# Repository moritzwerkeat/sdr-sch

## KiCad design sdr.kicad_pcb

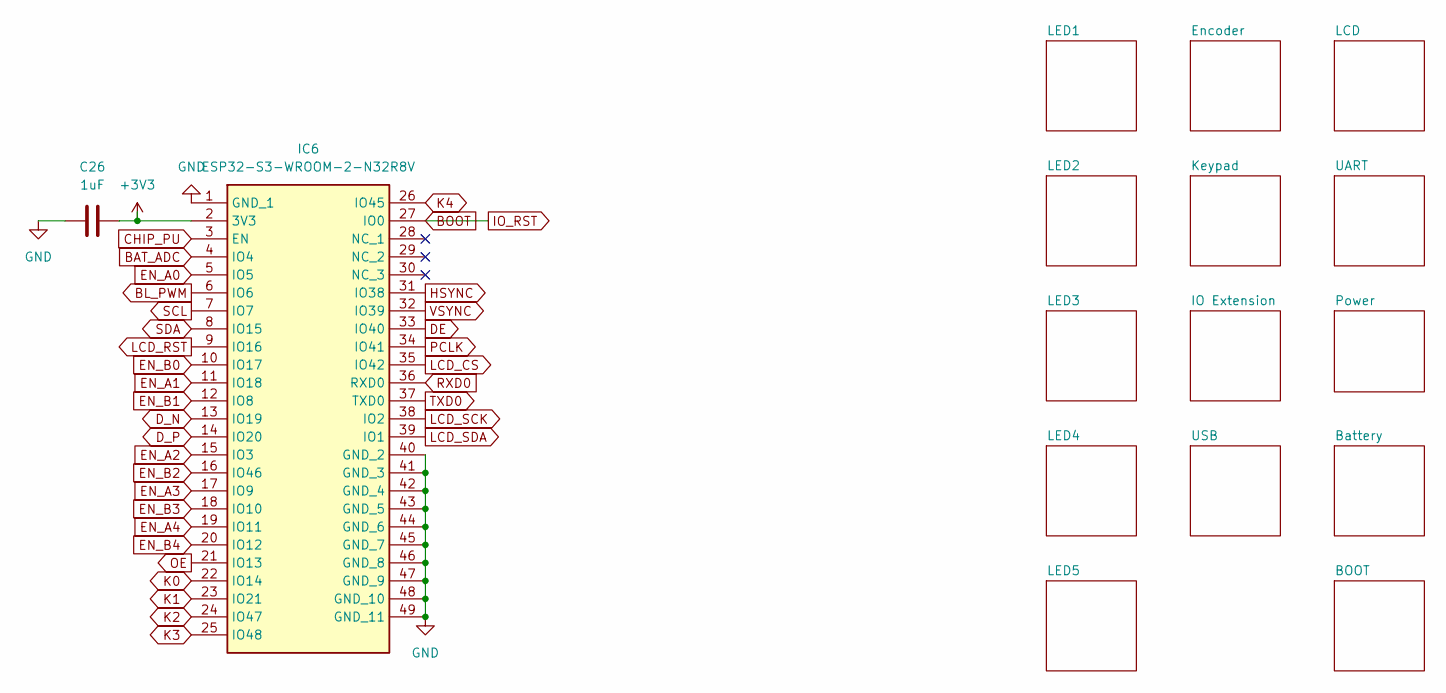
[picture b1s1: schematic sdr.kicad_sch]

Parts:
C26: 1uF; C_0603_1608Metric
IC6: ESP32-S3-WROOM-2-N32R8V; ESP32S3WROOM2N32R8V; Manufacturer_Part_Number ESP32-S3-WROOM-2-N32R8V; Mouser Part Number 356-ESP3S3WRM2N32R8V

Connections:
+3V3: C26.1, IC6.2 (3V3); also elsewhere on the board
BAT_ADC: IC6.4 (IO4); also elsewhere on the board
BL_PWM: IC6.6 (IO6); also elsewhere on the board
BOOT: IC6.27 (IO0); also elsewhere on the board
CHIP_PU: IC6.3 (EN); also elsewhere on the board
DE: IC6.33 (IO40); also elsewhere on the board
D_N: IC6.13 (IO19); also elsewhere on the board
D_P: IC6.14 (IO20); also elsewhere on the board
EN_A0: IC6.5 (IO5); also elsewhere on the board
EN_A1: IC6.11 (IO18); also elsewhere on the board
EN_A2: IC6.15 (IO3); also elsewhere on the board
EN_A3: IC6.17 (IO9); also elsewhere on the board
EN_A4: IC6.19 (IO11); also elsewhere on the board
EN_B0: IC6.10 (IO17); also elsewhere on the board
EN_B1: IC6.12 (IO8); also elsewhere on the board
EN_B2: IC6.16 (IO46); also elsewhere on the board
EN_B3: IC6.18 (IO10); also elsewhere on the board
EN_B4: IC6.20 (IO12); also elsewhere on the board
GND: C26.2, IC6.1 (GND_1), IC6.40 (GND_2), IC6.41 (GND_3), IC6.42 (GND_4), IC6.43 (GND_5), IC6.44 (GND_6), IC6.45 (GND_7), IC6.46 (GND_8), IC6.47 (GND_9), IC6.48 (GND_10), IC6.49 (GND_11); also elsewhere on the board
HSYNC: IC6.31 (IO38); also elsewhere on the board
K0: IC6.22 (IO14); also elsewhere on the board
K1: IC6.23 (IO21); also elsewhere on the board
K2: IC6.24 (IO47); also elsewhere on the board
K3: IC6.25 (IO48); also elsewhere on the board
K4: IC6.26 (IO45); also elsewhere on the board
LCD_CS: IC6.35 (IO42); also elsewhere on the board
LCD_RST: IC6.9 (IO16); also elsewhere on the board
LCD_SCK: IC6.38 (IO2); also elsewhere on the board
LCD_SDA: IC6.39 (IO1); also elsewhere on the board
OE: IC6.21 (IO13); also elsewhere on the board
PCLK: IC6.34 (IO41); also elsewhere on the board
RXD0: IC6.36 (RXD0); also elsewhere on the board
SCL: IC6.7 (IO7); also elsewhere on the board
SDA: IC6.8 (IO15); also elsewhere on the board
TXD0: IC6.37 (TXD0); also elsewhere on the board
VSYNC: IC6.32 (IO39); also elsewhere on the board

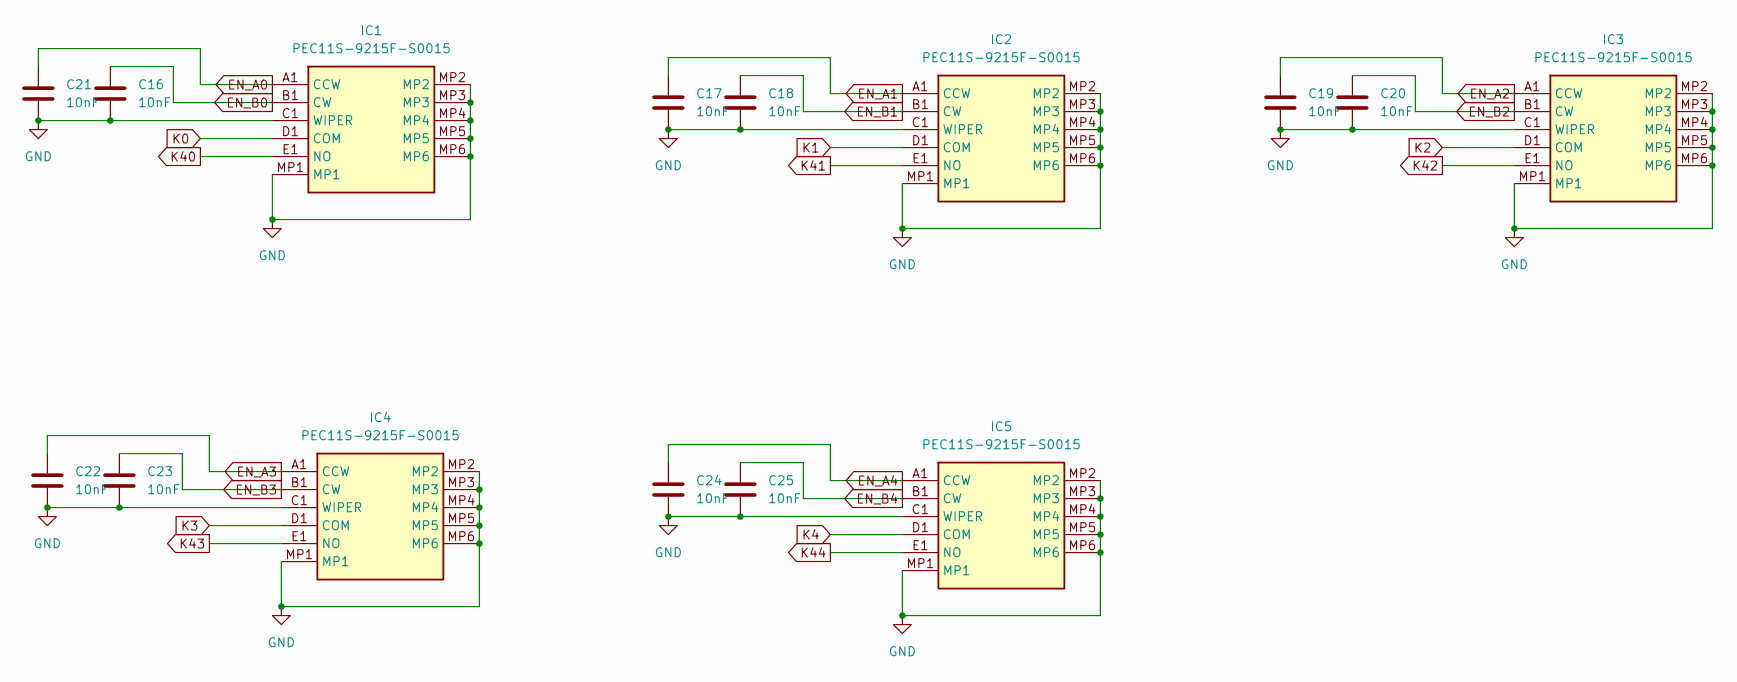
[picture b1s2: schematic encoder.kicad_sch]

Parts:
C16, C17, C18, C19, C20, C21, C22, C23, C24, C25: 10nF; C_0603_1608Metric
IC1, IC2, IC3, IC4, IC5: PEC11S-9215F-S0015; PEC11S9215FS0015; Manufacturer_Part_Number PEC11S-9215F-S0015; Mouser Part Number 652-PEC11S9215FS0015

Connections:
EN_A0: C21.1, IC1.A1 (CCW); also elsewhere on the board
EN_A1: C17.1, IC2.A1 (CCW); also elsewhere on the board
EN_A2: C19.1, IC3.A1 (CCW); also elsewhere on the board
EN_A3: C22.1, IC4.A1 (CCW); also elsewhere on the board
EN_A4: C24.1, IC5.A1 (CCW); also elsewhere on the board
EN_B0: C16.1, IC1.B1 (CW); also elsewhere on the board
EN_B1: C18.1, IC2.B1 (CW); also elsewhere on the board
EN_B2: C20.1, IC3.B1 (CW); also elsewhere on the board
EN_B3: C23.1, IC4.B1 (CW); also elsewhere on the board
EN_B4: C25.1, IC5.B1 (CW); also elsewhere on the board
GND: C16.2, C17.2, C18.2, C19.2, C20.2, C21.2, C22.2, C23.2, C24.2, C25.2, IC1.C1 (WIPER), IC1.MP1, IC1.MP2, IC1.MP3, IC1.MP4, IC1.MP5, IC1.MP6, IC2.C1 (WIPER), IC2.MP1, IC2.MP2, IC2.MP3, IC2.MP4, IC2.MP5, IC2.MP6, IC3.C1 (WIPER), IC3.MP1, IC3.MP2, IC3.MP3, IC3.MP4, IC3.MP5, IC3.MP6, IC4.C1 (WIPER), IC4.MP1, IC4.MP2, IC4.MP3, IC4.MP4, IC4.MP5, IC4.MP6, IC5.C1 (WIPER), IC5.MP1, IC5.MP2, IC5.MP3, IC5.MP4, IC5.MP5, IC5.MP6; also elsewhere on the board
K0: IC1.D1 (COM); also elsewhere on the board
K1: IC2.D1 (COM); also elsewhere on the board
K2: IC3.D1 (COM); also elsewhere on the board
K3: IC4.D1 (COM); also elsewhere on the board
K4: IC5.D1 (COM); also elsewhere on the board
K40: IC1.E1 (NO); also elsewhere on the board
K41: IC2.E1 (NO); also elsewhere on the board
K42: IC3.E1 (NO); also elsewhere on the board
K43: IC4.E1 (NO); also elsewhere on the board
K44: IC5.E1 (NO); also elsewhere on the board

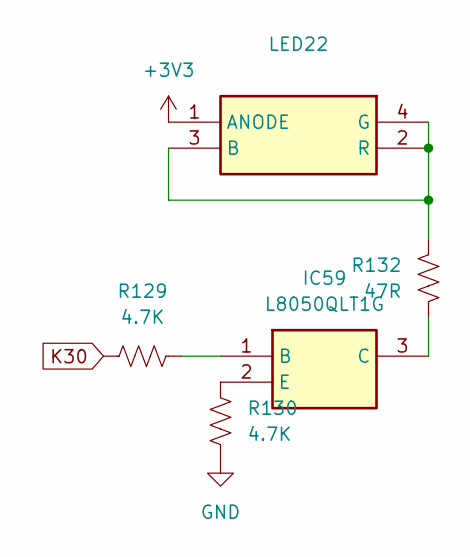
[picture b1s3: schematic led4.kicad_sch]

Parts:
IC59: L8050QLT1G; Manufacturer_Part_Number L8050QLT1G
LED22: LTRBR37G-4R4S-0125-0-2-R18; LTRBR37G4R4S012502R18; Manufacturer_Part_Number LTRBR37G-4R4S-0125-0-2-R18; Mouser Part Number 720-LTRBR37GA6714
R129, R130: 4.7K; R_0603_1608Metric
R132: 47R; R_0603_1608Metric

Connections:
+3V3: LED22.1 (ANODE); also elsewhere on the board
GND: R130.1; also elsewhere on the board
unnamed: IC59.1 (B), R129.2
unnamed: IC59.3 (C), R132.1
unnamed: IC59.2 (E), R130.2
unnamed: LED22.2 (R), LED22.3 (B), LED22.4 (G), R132.2

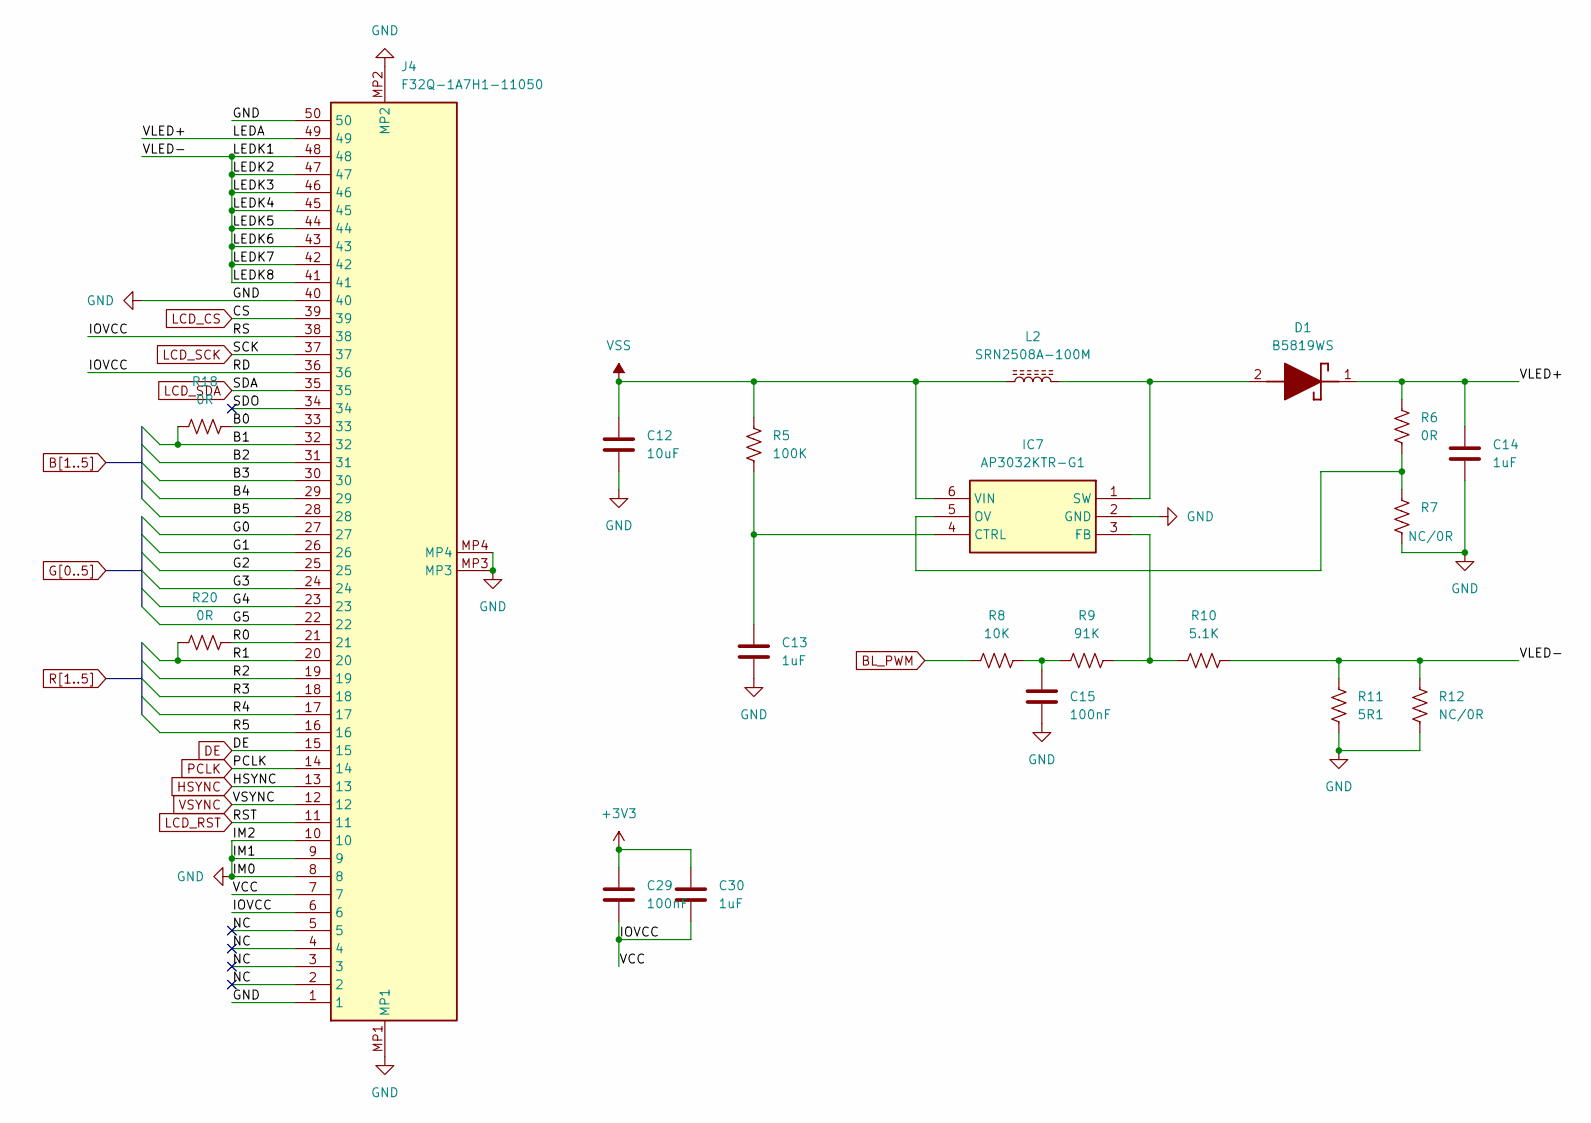
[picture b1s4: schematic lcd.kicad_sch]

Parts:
C12: 10uF; C_0603_1608Metric
C13, C14, C30: 1uF; C_0603_1608Metric
C15, C29: 100nF; C_0603_1608Metric
D1: B5819WS; SOD2613X100N; Manufacturer_Part_Number B5819WS
IC7: AP3032KTR-G1; SOT95P280X145-6N; Manufacturer_Part_Number AP3032KTR-G1; Mouser Part Number 621-AP3032KTR-G1
J4: F32Q-1A7H1-11050; F32Q1A7H111050; Manufacturer_Part_Number F32Q-1A7H1-11050; Mouser Part Number 649-F32Q-1A7H1-11050
L2: SRN2508A-100M; L_1008_2520Metric
R5: 100K; R_0603_1608Metric
R6, R18, R20: 0R; R_0603_1608Metric
R7, R12: NC/0R; R_0603_1608Metric
R8: 10K; R_0603_1608Metric
R9: 91K; R_0603_1608Metric
R10: 5.1K; R_0603_1608Metric
R11: 5R1; R_0603_1608Metric

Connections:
+3V3: C29.1, C30.1; also elsewhere on the board
/LCD/B0: J4.33, R18.2
/LCD/IOVCC: C29.2, C30.2, J4.6, J4.7, J4.36, J4.38
/LCD/LEDA: C14.1, D1.1 (K), J4.49, R6.1
/LCD/LEDK1: J4.41, J4.42, J4.43, J4.44, J4.45, J4.46, J4.47, J4.48, R10.2, R11.2, R12.2
/LCD/NC: J4.2, J4.3, J4.4, J4.5
/LCD/R0: J4.21, R20.2
/LCD/SDO: J4.34
B1: J4.32, R18.1; also elsewhere on the board
B2: J4.31; also elsewhere on the board
B3: J4.30; also elsewhere on the board
B4: J4.29; also elsewhere on the board
B5: J4.28; also elsewhere on the board
BL_PWM: R8.1; also elsewhere on the board
DE: J4.15; also elsewhere on the board
G0: J4.27; also elsewhere on the board
G1: J4.26; also elsewhere on the board
G2: J4.25; also elsewhere on the board
G3: J4.24; also elsewhere on the board
G4: J4.23; also elsewhere on the board
G5: J4.22; also elsewhere on the board
GND: C12.2, C13.2, C14.2, C15.2, IC7.2 (GND), J4.1, J4.8, J4.9, J4.10, J4.40, J4.50, J4.MP1, J4.MP2, J4.MP3, J4.MP4, R7.2, R11.1, R12.1; also elsewhere on the board
HSYNC: J4.13; also elsewhere on the board
LCD_CS: J4.39; also elsewhere on the board
LCD_RST: J4.11; also elsewhere on the board
LCD_SCK: J4.37; also elsewhere on the board
LCD_SDA: J4.35; also elsewhere on the board
unnamed: C15.1, R8.2, R9.1
unnamed: D1.2 (A), IC7.1 (SW), L2.2
unnamed: C13.1, IC7.4 (CTRL), R5.2
unnamed: IC7.3 (FB), R9.2, R10.1
unnamed: IC7.5 (OV), R6.2, R7.1
PCLK: J4.14; also elsewhere on the board
R1: J4.20, R20.1; also elsewhere on the board
R2: J4.19; also elsewhere on the board
R3: J4.18; also elsewhere on the board
R4: J4.17; also elsewhere on the board
R5: J4.16; also elsewhere on the board
VSS: C12.1, IC7.6 (VIN), L2.1, R5.1; also elsewhere on the board
VSYNC: J4.12; also elsewhere on the board

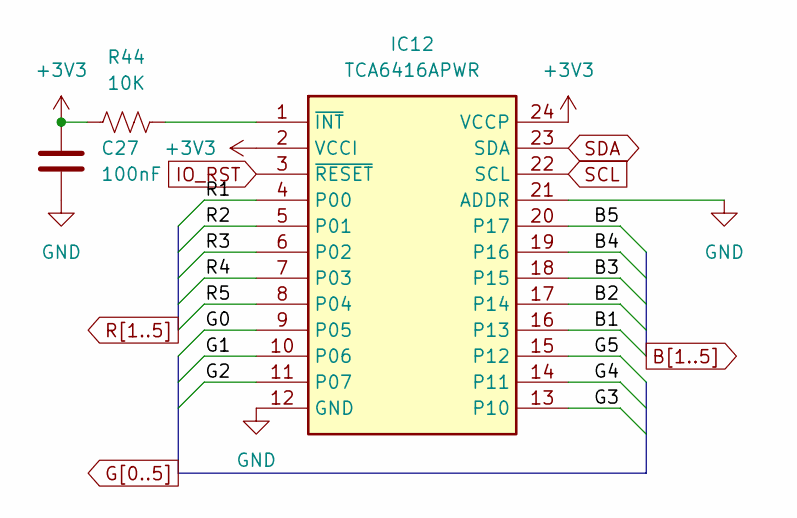
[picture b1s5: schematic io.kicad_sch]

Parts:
C27: 100nF; C_0603_1608Metric
IC12: TCA6416APWR; SOP65P640X120-24N; Manufacturer_Part_Number TCA6416APWR; Mouser Part Number 595-TCA6416APWR
R44: 10K; R_0603_1608Metric

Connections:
+3V3: C27.1, IC12.2 (VCCI), IC12.24 (VCCP), R44.1; also elsewhere on the board
B1: IC12.16 (P13); also elsewhere on the board
B2: IC12.17 (P14); also elsewhere on the board
B3: IC12.18 (P15); also elsewhere on the board
B4: IC12.19 (P16); also elsewhere on the board
B5: IC12.20 (P17); also elsewhere on the board
BOOT: IC12.3 (~RESET); also elsewhere on the board
G0: IC12.9 (P05); also elsewhere on the board
G1: IC12.10 (P06); also elsewhere on the board
G2: IC12.11 (P07); also elsewhere on the board
G3: IC12.13 (P10); also elsewhere on the board
G4: IC12.14 (P11); also elsewhere on the board
G5: IC12.15 (P12); also elsewhere on the board
GND: C27.2, IC12.12 (GND), IC12.21 (ADDR); also elsewhere on the board
unnamed: IC12.1 (~INT), R44.2
R1: IC12.4 (P00); also elsewhere on the board
R2: IC12.5 (P01); also elsewhere on the board
R3: IC12.6 (P02); also elsewhere on the board
R4: IC12.7 (P03); also elsewhere on the board
R5: IC12.8 (P04); also elsewhere on the board
SCL: IC12.22 (SCL); also elsewhere on the board
SDA: IC12.23 (SDA); also elsewhere on the board

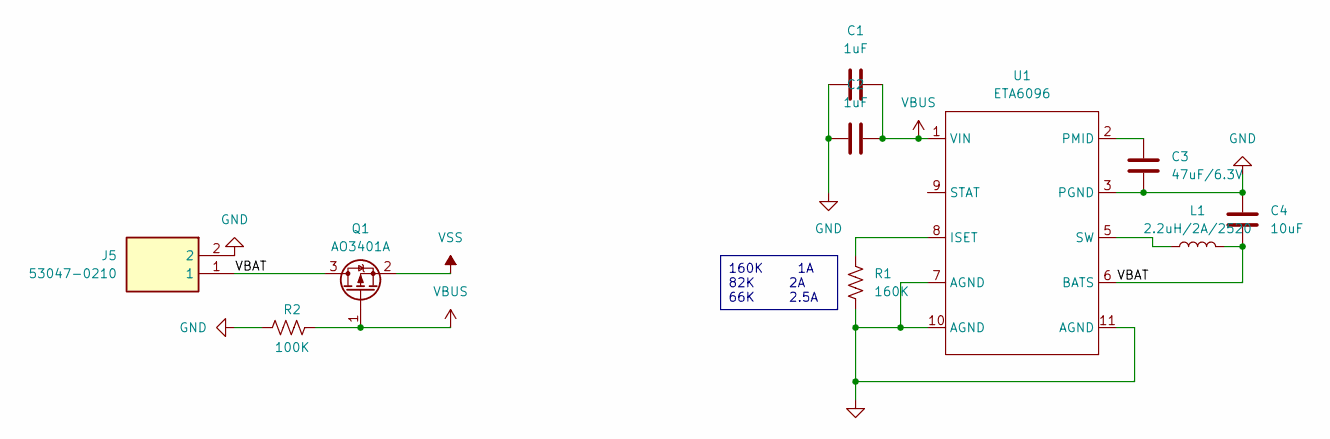
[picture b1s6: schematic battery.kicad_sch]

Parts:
C1, C2: 1uF; C_0603_1608Metric
C3: 47uF/6.3V; C_0603_1608Metric
C4: 10uF; C_0603_1608Metric
J5: 53047-0210; 530470210; Manufacturer_Part_Number 53047-0210; Mouser Part Number 538-53047-0210
L1: 2.2uH/2A/2520; L_1008_2520Metric
Q1: AO3401A; SOT-23
R1: 160K; R_0603_1608Metric
R2: 100K; R_0603_1608Metric
U1: ETA6096; SON50P300X300X90-11N

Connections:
/Battery/VBAT: C4.2, J5.1, L1.2, Q1.3 (D), U1.6 (BATS)
GND: C1.2, C2.2, C3.2, C4.1, J5.2, R1.1, R2.1, U1.3 (PGND), U1.7 (AGND), U1.10 (AGND), U1.11 (AGND); also elsewhere on the board
unnamed: R1.2, U1.8 (ISET)
unnamed: C3.1, U1.2 (PMID)
unnamed: L1.1, U1.5 (SW)
VBUS: C1.1, C2.1, Q1.1 (G), R2.2, U1.1 (VIN); also elsewhere on the board
VSS: Q1.2 (S); also elsewhere on the board

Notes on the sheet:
160K 1A 82K 2A 66K 2.5A

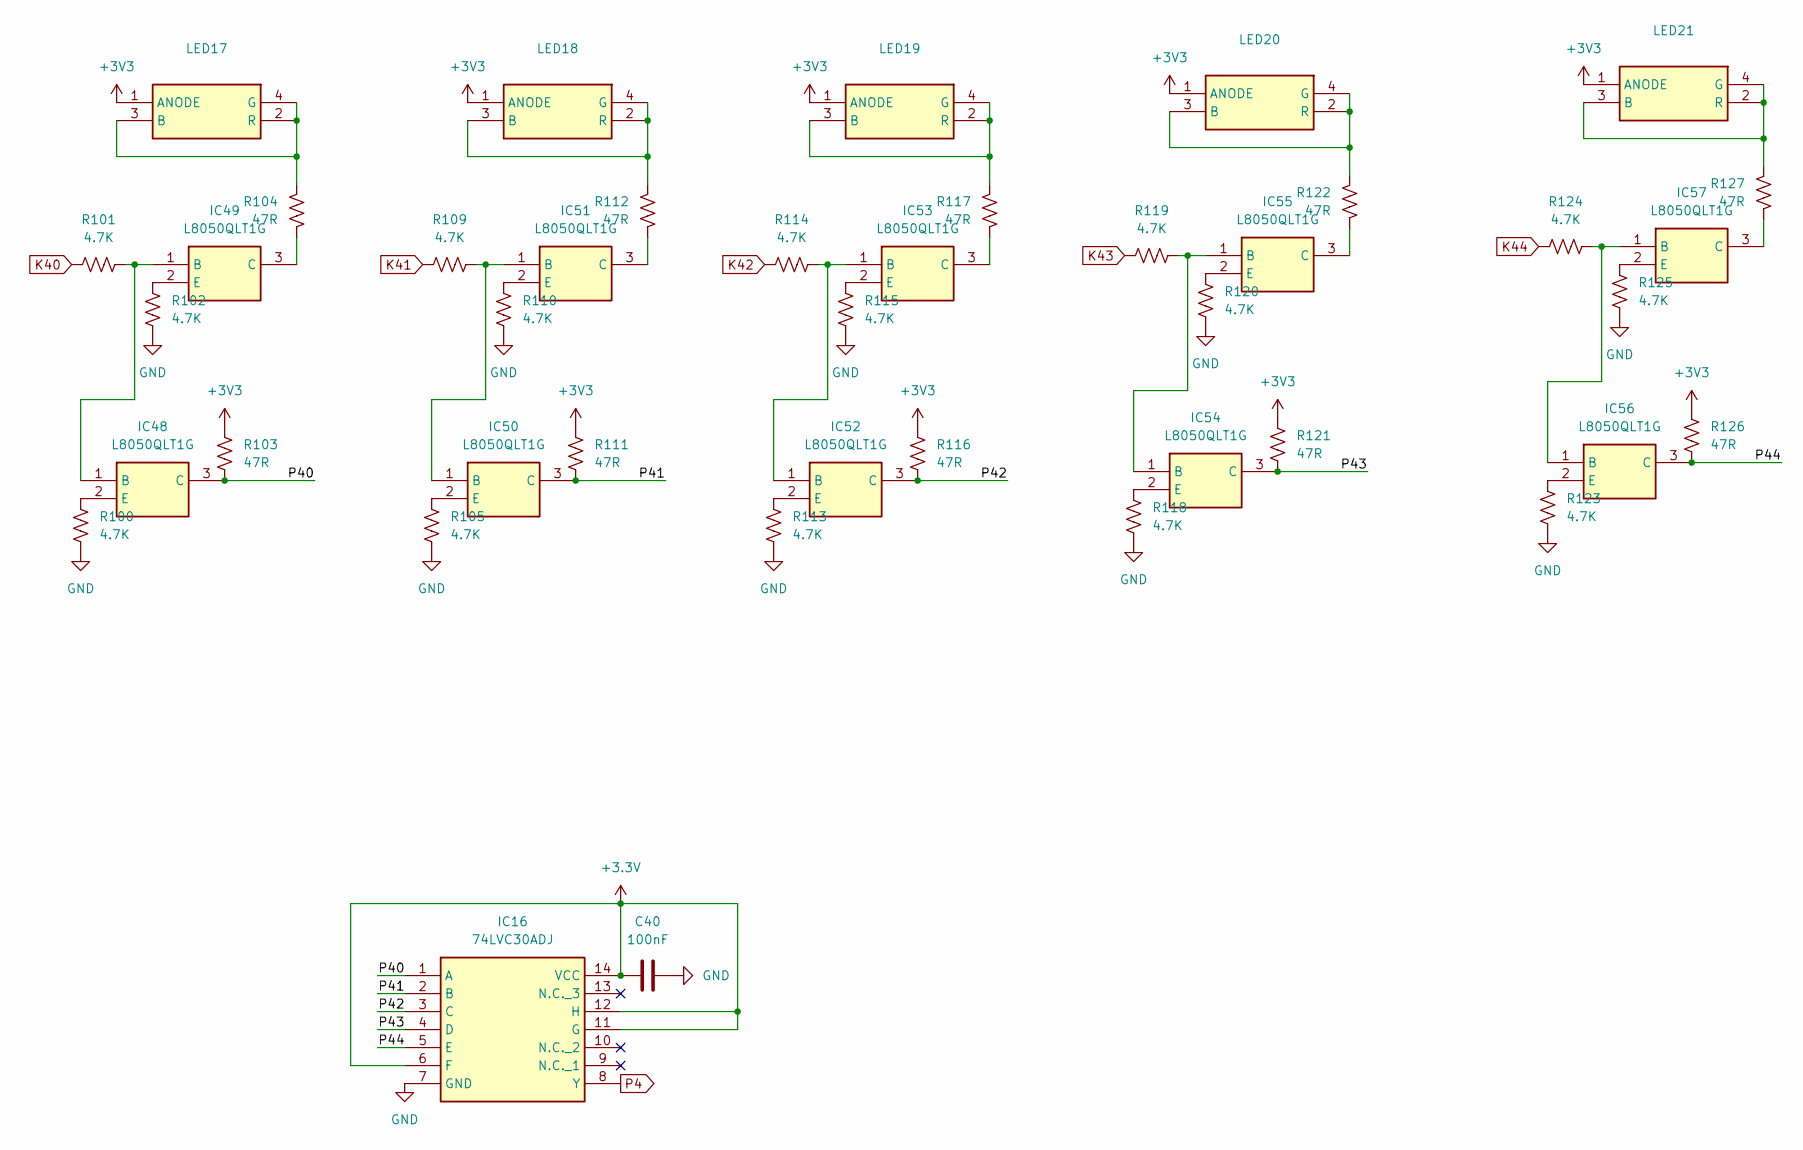
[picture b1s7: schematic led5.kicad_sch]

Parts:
C40: 100nF; C_0603_1608Metric
IC16: 74LVC30ADJ; SOIC127P600X175-14N; Manufacturer_Part_Number 74LVC30ADJ; Mouser Part Number 771-74LVC30ADJ
IC48, IC49, IC50, IC51, IC52, IC53, IC54, IC55, IC56, IC57: L8050QLT1G; Manufacturer_Part_Number L8050QLT1G
LED17, LED18, LED19, LED20, LED21: LTRBR37G-4R4S-0125-0-2-R18; LTRBR37G4R4S012502R18; Manufacturer_Part_Number LTRBR37G-4R4S-0125-0-2-R18; Mouser Part Number 720-LTRBR37GA6714
R100, R101, R102, R105, R109, R110, R113, R114, R115, R118, R119, R120, R123, R124, R125: 4.7K; R_0603_1608Metric
R103, R104, R111, R112, R116, R117, R121, R122, R126, R127: 47R; R_0603_1608Metric

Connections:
+3.3V: C40.1, IC16.6 (F), IC16.11 (G), IC16.12 (H), IC16.14 (VCC); also elsewhere on the board
+3V3: LED17.1 (ANODE), LED18.1 (ANODE), LED19.1 (ANODE), LED20.1 (ANODE), LED21.1 (ANODE), R103.2, R111.2, R116.2, R121.2, R126.2; also elsewhere on the board
/LED5/P40: IC16.1 (A), IC48.3 (C), R103.1
/LED5/P41: IC16.2 (B), IC50.3 (C), R111.1
/LED5/P42: IC16.3 (C), IC52.3 (C), R116.1
/LED5/P43: IC16.4 (D), IC54.3 (C), R121.1
/LED5/P44: IC16.5 (E), IC56.3 (C), R126.1
GND: C40.2, IC16.7 (GND), R100.1, R102.1, R105.1, R110.1, R113.1, R115.1, R118.1, R120.1, R123.1, R125.1; also elsewhere on the board
K40: R101.1; also elsewhere on the board
K41: R109.1; also elsewhere on the board
K42: R114.1; also elsewhere on the board
K43: R119.1; also elsewhere on the board
K44: R124.1; also elsewhere on the board
unnamed: IC48.1 (B), IC49.1 (B), R101.2
unnamed: IC48.2 (E), R100.2
unnamed: IC49.3 (C), R104.1
unnamed: IC49.2 (E), R102.2
unnamed: IC50.1 (B), IC51.1 (B), R109.2
unnamed: IC50.2 (E), R105.2
unnamed: IC51.3 (C), R112.1
unnamed: IC51.2 (E), R110.2
unnamed: IC52.1 (B), IC53.1 (B), R114.2
unnamed: IC52.2 (E), R113.2
unnamed: IC53.3 (C), R117.1
unnamed: IC53.2 (E), R115.2
unnamed: IC54.1 (B), IC55.1 (B), R119.2
unnamed: IC54.2 (E), R118.2
unnamed: IC55.3 (C), R122.1
unnamed: IC55.2 (E), R120.2
unnamed: IC56.1 (B), IC57.1 (B), R124.2
unnamed: IC56.2 (E), R123.2
unnamed: IC57.3 (C), R127.1
unnamed: IC57.2 (E), R125.2
unnamed: LED17.2 (R), LED17.3 (B), LED17.4 (G), R104.2
unnamed: LED18.2 (R), LED18.3 (B), LED18.4 (G), R112.2
unnamed: LED19.2 (R), LED19.3 (B), LED19.4 (G), R117.2
unnamed: LED20.2 (R), LED20.3 (B), LED20.4 (G), R122.2
unnamed: LED21.2 (R), LED21.3 (B), LED21.4 (G), R127.2
P4: IC16.8 (Y); also elsewhere on the board

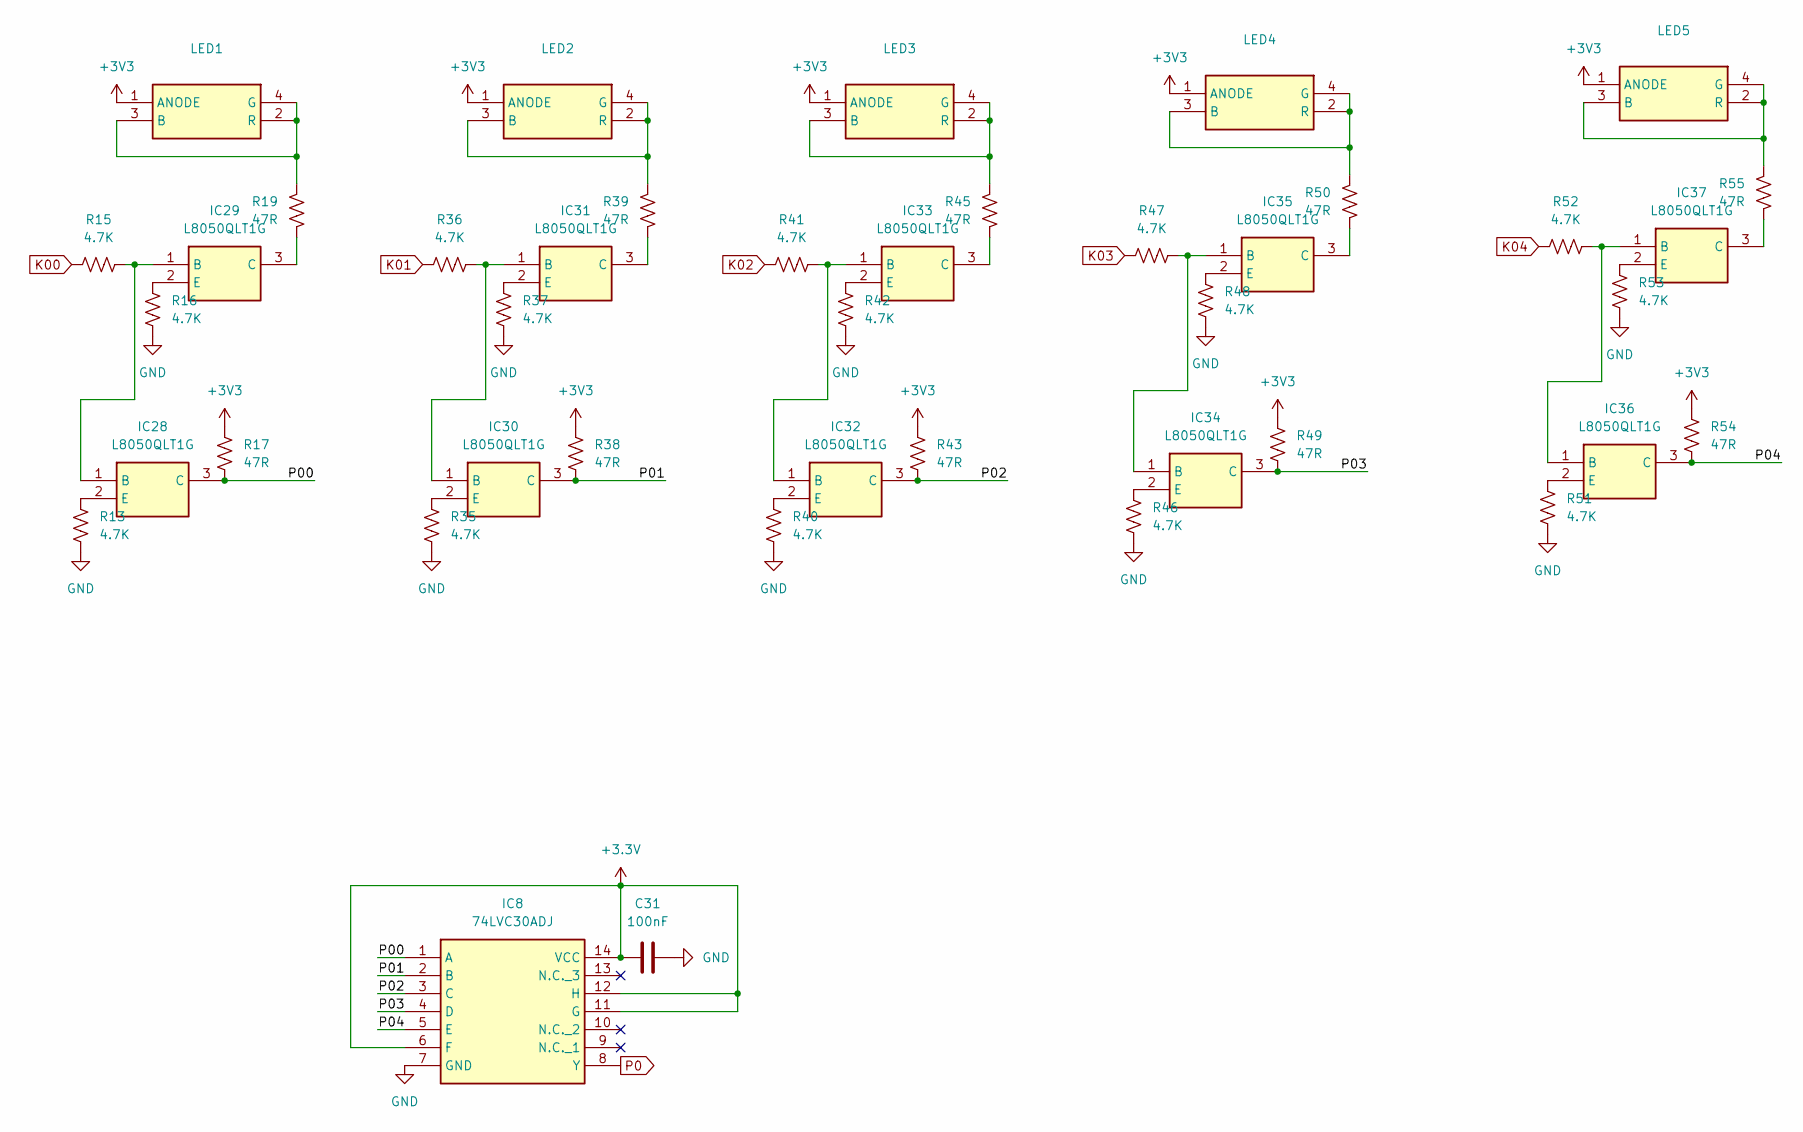
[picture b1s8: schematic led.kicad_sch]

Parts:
C31: 100nF; C_0603_1608Metric
IC8: 74LVC30ADJ; SOIC127P600X175-14N; Manufacturer_Part_Number 74LVC30ADJ; Mouser Part Number 771-74LVC30ADJ
IC28, IC29, IC30, IC31, IC32, IC33, IC34, IC35, IC36, IC37: L8050QLT1G; Manufacturer_Part_Number L8050QLT1G
LED1, LED2, LED3, LED4, LED5: LTRBR37G-4R4S-0125-0-2-R18; LTRBR37G4R4S012502R18; Manufacturer_Part_Number LTRBR37G-4R4S-0125-0-2-R18; Mouser Part Number 720-LTRBR37GA6714
R13, R15, R16, R35, R36, R37, R40, R41, R42, R46, R47, R48, R51, R52, R53: 4.7K; R_0603_1608Metric
R17, R19, R38, R39, R43, R45, R49, R50, R54, R55: 47R; R_0603_1608Metric

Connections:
+3.3V: C31.1, IC8.6 (F), IC8.11 (G), IC8.12 (H), IC8.14 (VCC); also elsewhere on the board
+3V3: LED1.1 (ANODE), LED2.1 (ANODE), LED3.1 (ANODE), LED4.1 (ANODE), LED5.1 (ANODE), R17.2, R38.2, R43.2, R49.2, R54.2; also elsewhere on the board
/LED1/P00: IC8.1 (A), IC28.3 (C), R17.1
/LED1/P01: IC8.2 (B), IC30.3 (C), R38.1
/LED1/P02: IC8.3 (C), IC32.3 (C), R43.1
/LED1/P03: IC8.4 (D), IC34.3 (C), R49.1
/LED1/P04: IC8.5 (E), IC36.3 (C), R54.1
GND: C31.2, IC8.7 (GND), R13.1, R16.1, R35.1, R37.1, R40.1, R42.1, R46.1, R48.1, R51.1, R53.1; also elsewhere on the board
K00: R15.1; also elsewhere on the board
K01: R36.1; also elsewhere on the board
K02: R41.1; also elsewhere on the board
K03: R47.1; also elsewhere on the board
K04: R52.1; also elsewhere on the board
unnamed: IC28.1 (B), IC29.1 (B), R15.2
unnamed: IC28.2 (E), R13.2
unnamed: IC29.3 (C), R19.1
unnamed: IC29.2 (E), R16.2
unnamed: IC30.1 (B), IC31.1 (B), R36.2
unnamed: IC30.2 (E), R35.2
unnamed: IC31.3 (C), R39.1
unnamed: IC31.2 (E), R37.2
unnamed: IC32.1 (B), IC33.1 (B), R41.2
unnamed: IC32.2 (E), R40.2
unnamed: IC33.3 (C), R45.1
unnamed: IC33.2 (E), R42.2
unnamed: IC34.1 (B), IC35.1 (B), R47.2
unnamed: IC34.2 (E), R46.2
unnamed: IC35.3 (C), R50.1
unnamed: IC35.2 (E), R48.2
unnamed: IC36.1 (B), IC37.1 (B), R52.2
unnamed: IC36.2 (E), R51.2
unnamed: IC37.3 (C), R55.1
unnamed: IC37.2 (E), R53.2
unnamed: LED1.2 (R), LED1.3 (B), LED1.4 (G), R19.2
unnamed: LED2.2 (R), LED2.3 (B), LED2.4 (G), R39.2
unnamed: LED3.2 (R), LED3.3 (B), LED3.4 (G), R45.2
unnamed: LED4.2 (R), LED4.3 (B), LED4.4 (G), R50.2
unnamed: LED5.2 (R), LED5.3 (B), LED5.4 (G), R55.2
P0: IC8.8 (Y); also elsewhere on the board

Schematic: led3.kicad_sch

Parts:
C38: 100nF; C_0603_1608Metric
IC14: 74LVC30ADJ; SOIC127P600X175-14N; Manufacturer_Part_Number 74LVC30ADJ; Mouser Part Number 771-74LVC30ADJ
IC38, IC39, IC40, IC41, IC42, IC43, IC44, IC45, IC46, IC47: L8050QLT1G; Manufacturer_Part_Number L8050QLT1G
LED11, LED12, LED13, LED14, LED15: LTRBR37G-4R4S-0125-0-2-R18; LTRBR37G4R4S012502R18; Manufacturer_Part_Number LTRBR37G-4R4S-0125-0-2-R18; Mouser Part Number 720-LTRBR37GA6714
R75, R76, R77, R80, R81, R82, R85, R86, R87, R90, R91, R92, R95, R96, R97: 4.7K; R_0603_1608Metric
R78, R79, R83, R84, R88, R89, R93, R94, R98, R99: 47R; R_0603_1608Metric

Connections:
+3.3V: C38.1, IC14.6 (F), IC14.11 (G), IC14.12 (H), IC14.14 (VCC); also elsewhere on the board
+3V3: LED11.1 (ANODE), LED12.1 (ANODE), LED13.1 (ANODE), LED14.1 (ANODE), LED15.1 (ANODE), R78.2, R83.2, R88.2, R93.2, R98.2; also elsewhere on the board
/LED3/P20: IC14.1 (A), IC38.3 (C), R78.1
/LED3/P21: IC14.2 (B), IC40.3 (C), R83.1
/LED3/P22: IC14.3 (C), IC42.3 (C), R88.1
/LED3/P23: IC14.4 (D), IC44.3 (C), R93.1
/LED3/P24: IC14.5 (E), IC46.3 (C), R98.1
GND: C38.2, IC14.7 (GND), R75.1, R77.1, R80.1, R82.1, R85.1, R87.1, R90.1, R92.1, R95.1, R97.1; also elsewhere on the board
K20: R76.1; also elsewhere on the board
K21: R81.1; also elsewhere on the board
K22: R86.1; also elsewhere on the board
K23: R91.1; also elsewhere on the board
K24: R96.1; also elsewhere on the board
unnamed: IC38.1 (B), IC39.1 (B), R76.2
unnamed: IC38.2 (E), R75.2
unnamed: IC39.3 (C), R79.1
unnamed: IC39.2 (E), R77.2
unnamed: IC40.1 (B), IC41.1 (B), R81.2
unnamed: IC40.2 (E), R80.2
unnamed: IC41.3 (C), R84.1
unnamed: IC41.2 (E), R82.2
unnamed: IC42.1 (B), IC43.1 (B), R86.2
unnamed: IC42.2 (E), R85.2
unnamed: IC43.3 (C), R89.1
unnamed: IC43.2 (E), R87.2
unnamed: IC44.1 (B), IC45.1 (B), R91.2
unnamed: IC44.2 (E), R90.2
unnamed: IC45.3 (C), R94.1
unnamed: IC45.2 (E), R92.2
unnamed: IC46.1 (B), IC47.1 (B), R96.2
unnamed: IC46.2 (E), R95.2
unnamed: IC47.3 (C), R99.1
unnamed: IC47.2 (E), R97.2
unnamed: LED11.2 (R), LED11.3 (B), LED11.4 (G), R79.2
unnamed: LED12.2 (R), LED12.3 (B), LED12.4 (G), R84.2
unnamed: LED13.2 (R), LED13.3 (B), LED13.4 (G), R89.2
unnamed: LED14.2 (R), LED14.3 (B), LED14.4 (G), R94.2
unnamed: LED15.2 (R), LED15.3 (B), LED15.4 (G), R99.2
P2: IC14.8 (Y); also elsewhere on the board

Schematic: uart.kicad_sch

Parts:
C5, C34: 1uF; C_0603_1608Metric
C6: 10uF/25V; C_0603_1608Metric
D4: B5819WS; SOD2613X100N; Manufacturer_Part_Number B5819WS
IC10, IC11: L8050QLT1G; Manufacturer_Part_Number L8050QLT1G
IC17: CP2102N-A02-GQFN28; QFN50P500X500X80-29N-D; Manufacturer_Part_Number CP2102N-A02-GQFN28; Mouser Part Number 634-CP2102NA02GQFN28
J2: USB4110-GF-A; USB4110GFA; Manufacturer_Part_Number USB4110-GF-A; Mouser Part Number 640-USB4110-GF-A
R25, R26: 5.1K; R_0603_1608Metric
R31, R32: 10K(1%); R_0603_1608Metric
R33, R34, R138, R139: 0(1%); R_0603_1608Metric
R134: 1K(1%); R_0603_1608Metric
R135: 22.1K(1%); R_0603_1608Metric
R136: 47.5K(1%); R_0603_1608Metric
R137: 10K(1%)(NC); R_0603_1608Metric

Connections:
+3V3: C6.1, IC17.6 (VDD), IC17.7 (VREGIN), R134.1; also elsewhere on the board
/UART/DTR: IC11.2 (E), R31.1
/UART/RTS: IC10.2 (E), IC17.24 (RTS), R32.1
/UART/USB_DN: IC17.5 (D-), J2.A7, J2.B7
/UART/USB_DP: IC17.4 (D+), J2.A6, J2.B6
BOOT: R34.2; also elsewhere on the board
CHIP_PU: R33.2; also elsewhere on the board
GND: C5.2, C6.2, C34.2, IC17.3 (GND), J2.A1, J2.A12, J2.B12, J2.MP1, J2.MP2, J2.MP3, J2.MP4, R25.2, R26.2, R136.2, R137.2; also elsewhere on the board
unnamed: IC10.1 (B), R31.2
unnamed: IC10.3 (C), R33.1
unnamed: IC11.1 (B), R32.2
unnamed: IC11.3 (C), R34.1
unnamed: IC17.9 (RSTB), R134.2
unnamed: IC17.25 (RXD), R138.2
unnamed: IC17.11 (SUSPENDB), R137.1
unnamed: IC17.26 (TXD), R139.1
unnamed: C5.1, IC17.8 (VBUS), R135.2, R136.1
unnamed: J2.A5, R25.1
unnamed: J2.B5, R26.1
RXD0: R139.2; also elsewhere on the board
TXD0: R138.1; also elsewhere on the board
VBUS: C34.1, D4.2 (A), J2.A4, J2.A9, J2.B9, R135.1; also elsewhere on the board
VSS: D4.1 (K); also elsewhere on the board

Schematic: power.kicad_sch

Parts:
C10, C11: 100nF; C_0603_1608Metric
C39: 22uF; C_0603_1608Metric
C41, C42: 100nF/50V; C_0603_1608Metric
C43, C44: 100uF/4V; CP_EIA-1608-08_AVX-J
IC15: AP63203WU-7; AP63203WU7; Manufacturer_Part_Number AP63203WU-7; Mouser Part Number 621-AP63203WU-7
L4: SRP2510A-4R7M; L_1008_2520Metric
R3, R4: 100K; R_0603_1608Metric

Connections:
+3V3: C42.1, C43.1, C44.1, IC15.1 (FB), L4.2; also elsewhere on the board
BAT_ADC: C11.1, R3.2, R4.1; also elsewhere on the board
GND: C10.2, C11.2, C39.2, C42.2, C43.2, C44.2, IC15.4 (GND), R4.2; also elsewhere on the board
unnamed: C41.1, IC15.6 (BST)
unnamed: C41.2, IC15.5 (SW), L4.1
VSS: C10.1, C39.1, IC15.2 (EN), IC15.3 (VIN), R3.1; also elsewhere on the board

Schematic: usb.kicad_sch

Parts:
C32: 1uF; C_0603_1608Metric
D2: B5819WS; SOD2613X100N; Manufacturer_Part_Number B5819WS
J1: USB4145-03-0230-C; USB4145030230C; Manufacturer_Part_Number USB4145-03-0230-C; Mouser Part Number 640-USB4145-3-0230-C
R21: 5.1K; R_0603_1608Metric
R22: 5.1K; C_0603_1608Metric

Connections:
D_N: J1.A7 (DN1), J1.B7 (DN2); also elsewhere on the board
D_P: J1.A6 (DP1), J1.B6 (DP2); also elsewhere on the board
GND: C32.1, J1.A1 (GND_1), J1.A12 (GND_2), J1.B1 (GND_3), J1.B12 (GND_4), J1.MH1 (MH5), J1.MH2 (MH6), J1.MH3, J1.MH4, R21.2, R22.2; also elsewhere on the board
unnamed: J1.A5 (CC1), R22.1
unnamed: J1.B5 (CC2), R21.1
VBUS: C32.2, D2.2 (A), J1.A4 (VBUS_1), J1.A9 (VBUS_2), J1.B4 (VBUS_3), J1.B9 (VBUS_4); also elsewhere on the board
VSS: D2.1 (K); also elsewhere on the board

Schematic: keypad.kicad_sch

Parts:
IC9: 74HC541D; SOIC127P1030X250-20N; Manufacturer_Part_Number 74HC541D; Mouser Part Number 757-74HC541D
K5, K6, K7, K8, K9, K10, K11, K12, K13, K14, K15, K16, K17, K18, K19, K20, K21, K22, K23, K24, K25, K26, K27, K28, K29, K30, K31, K32, K33, K34, K35, K36: TASTE_GROSS

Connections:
+3V3: IC9.20 (VCC); also elsewhere on the board
GND: IC9.10 (GND); also elsewhere on the board
K0: IC9.18 (Y1), K5.P$2 (S), K5.P$3 (S), K6.P$2 (S), K6.P$3 (S), K15.P$2 (S), K15.P$3 (S), K16.P$2 (S), K16.P$3 (S), K25.P$2 (S), K25.P$3 (S), K26.P$2 (S), K26.P$3 (S), K35.P$2 (S), K35.P$3 (S), K36.P$2 (S), K36.P$3 (S); also elsewhere on the board
K00: K5.P$1, K6.P$1; also elsewhere on the board
K1: IC9.17 (Y2), K7.P$2 (S), K7.P$3 (S), K8.P$2 (S), K8.P$3 (S), K17.P$2 (S), K17.P$3 (S), K18.P$2 (S), K18.P$3 (S), K27.P$2 (S), K27.P$3 (S), K28.P$2 (S), K28.P$3 (S); also elsewhere on the board
K01: K7.P$1, K8.P$1; also elsewhere on the board
K2: IC9.16 (Y3), K9.P$2 (S), K9.P$3 (S), K10.P$2 (S), K10.P$3 (S), K19.P$2 (S), K19.P$3 (S), K20.P$2 (S), K20.P$3 (S), K29.P$2 (S), K29.P$3 (S), K30.P$2 (S), K30.P$3 (S); also elsewhere on the board
K02: K9.P$1, K10.P$1; also elsewhere on the board
K3: IC9.15 (Y4), K11.P$2 (S), K11.P$3 (S), K12.P$2 (S), K12.P$3 (S), K21.P$2 (S), K21.P$3 (S), K22.P$2 (S), K22.P$3 (S), K31.P$2 (S), K31.P$3 (S), K32.P$2 (S), K32.P$3 (S); also elsewhere on the board
K03: K11.P$1, K12.P$1; also elsewhere on the board
K04: K13.P$1, K14.P$1; also elsewhere on the board
K4: IC9.14 (Y5), K13.P$2 (S), K13.P$3 (S), K14.P$2 (S), K14.P$3 (S), K23.P$2 (S), K23.P$3 (S), K24.P$2 (S), K24.P$3 (S), K33.P$2 (S), K33.P$3 (S), K34.P$2 (S), K34.P$3 (S); also elsewhere on the board
K10: K15.P$1, K16.P$1; also elsewhere on the board
K11: K17.P$1, K18.P$1; also elsewhere on the board
K12: K19.P$1, K20.P$1; also elsewhere on the board
K13: K21.P$1, K22.P$1; also elsewhere on the board
K14: K23.P$1, K24.P$1; also elsewhere on the board
K20: K25.P$1, K26.P$1; also elsewhere on the board
K21: K27.P$1, K28.P$1; also elsewhere on the board
K22: K29.P$1, K30.P$1; also elsewhere on the board
K23: K31.P$1, K32.P$1; also elsewhere on the board
K24: K33.P$1, K34.P$1; also elsewhere on the board
OE: IC9.1 (~G1), IC9.19 (~G2); also elsewhere on the board
P0: IC9.2 (A1); also elsewhere on the board
P1: IC9.3 (A2); also elsewhere on the board
P2: IC9.4 (A3); also elsewhere on the board
P4: IC9.6 (A5); also elsewhere on the board

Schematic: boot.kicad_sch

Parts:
C28: 1uF/16V(10%); C_0603_1608Metric
C35, C36: 0.1uF/50V(10%)(NC); C_0603_1608Metric
R14: 10K(1%); R_0603_1608Metric
S1, S2: NTC013-AT1J-A160T; NTC013AT1JA160T; Manufacturer_Part_Number NTC013-AT1J-A160T

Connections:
+3V3: R14.1; also elsewhere on the board
BOOT: C35.2, S1.3 (COM_1); also elsewhere on the board
CHIP_PU: C28.1, C36.2, R14.2, S2.3 (COM_1); also elsewhere on the board
GND: C28.2, C35.1, C36.1, S1.1 (NO_1), S2.1 (NO_1); also elsewhere on the board

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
